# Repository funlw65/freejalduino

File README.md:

[Go back to the main site](https://funlw65.github.io/)
<hr />

## :boom: Welcome!

An alternative to the Arduino board, featuring the PIC18F2550 microcontroller.

Project created using Eagle 7.5.0.

```
 Page done.
```

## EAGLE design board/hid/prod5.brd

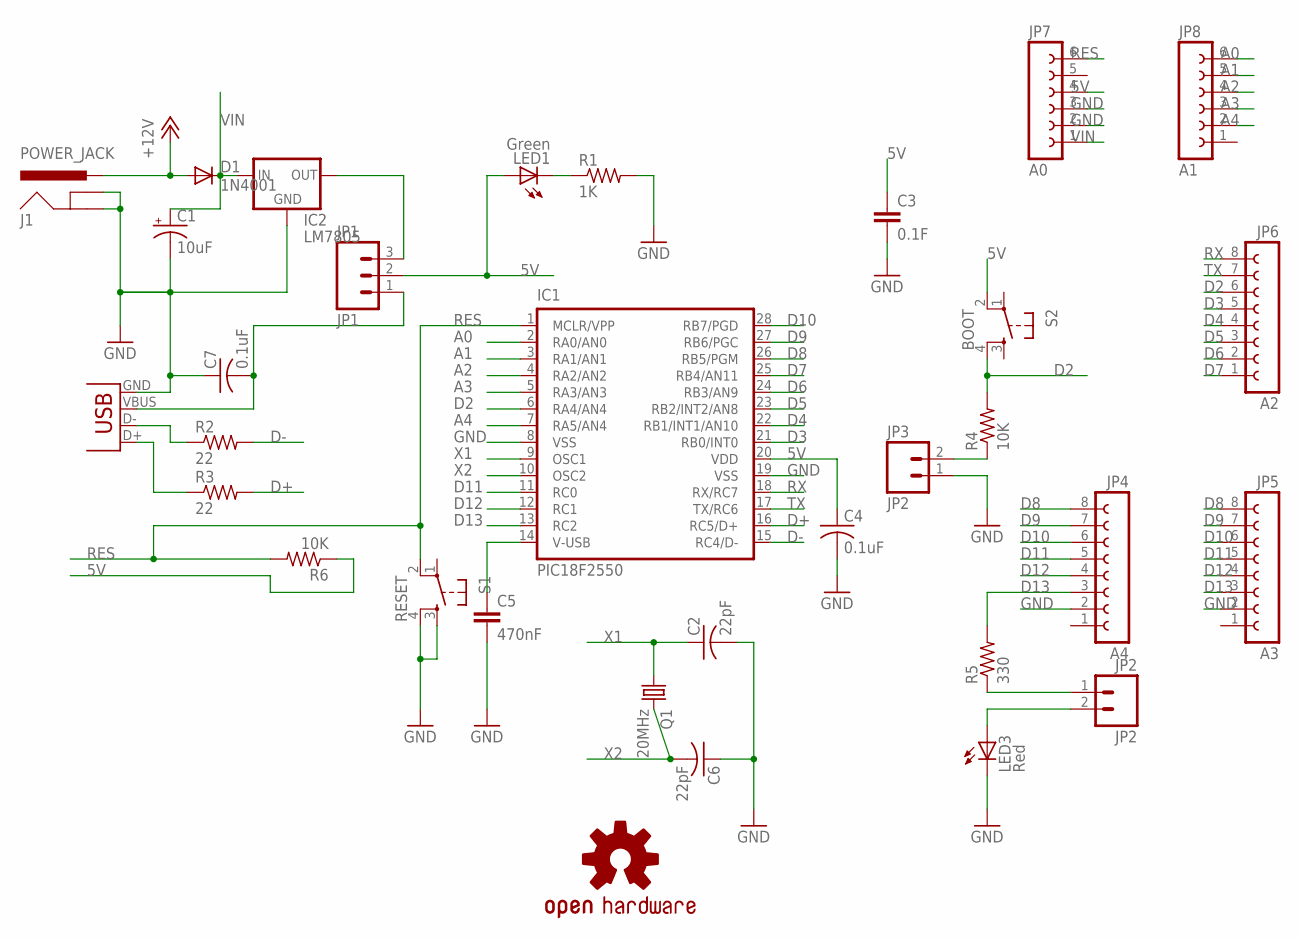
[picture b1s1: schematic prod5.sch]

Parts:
C1: 10uF; CPOL-RADIAL-10UF-25V
C2, C6: 22pF; C025-025X050
C3: 0.1F; CAP-PTH-5MM
C4, C7: 0.1uF; C025-025X050
C5: 470nF; CAP-PTH-5MM
D1: 1N4001; DIODE-1N4001
IC1: PIC18F2550; DIL28-3
IC2: LM7805; 78XXL
J1: POWER_JACK; POWER_JACK_PTH
JP1: JP1; 1X03
JP2, JP3: JP2; 1X02
JP4: A4; FE08
JP5: A3; FE08
JP6: A2; FE08
JP7: A0; FE06
JP8: A1; FE06
LED1: Green; LED3MM
LED3: Red; LED3MM
LOGO1: OSHW-LOGOM; OSHW-LOGO-M
Q1: 20MHz; HC49/S
R1: 1K; 0204/7
R2, R3: 22; 0207/15
R4: 10K; 0207/15
R5: 330; 0204/7
R6: 10K; 0204/7
S1: RESET; TACTILE-PTH
S2: BOOT; TACTILE-PTH
X1: USBPTH; USB-B-PTH

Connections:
5V: C3.1, C4.1, IC1.20 (VDD), JP1.2, JP7.4, LED1.A, R6.1, S2.2
+12V: D1.A, J1.PWR
A0: IC1.2 (RA0/AN0), JP8.6
A1: IC1.3 (RA1/AN1), JP8.5
A2: IC1.4 (RA2/AN2), JP8.4
A3: IC1.5 (RA3/AN3), JP8.3
A4: IC1.7 (RA5/AN4), JP8.2
D2: IC1.6 (RA4/AN4), JP6.6, R4.2, S2.4
D3: IC1.21 (RB0/INT0), JP6.5
D4: IC1.22 (RB1/INT1/AN10), JP6.4
D5: IC1.23 (RB2/INT2/AN8), JP6.3
D6: IC1.24 (RB3/AN9), JP6.2
D7: IC1.25 (RB4/AN11), JP6.1
D8: IC1.26 (RB5/PGM), JP4.8, JP5.8
D9: IC1.27 (RB6/PGC), JP4.7, JP5.7
D10: IC1.28 (RB7/PGD), JP4.6, JP5.6
D11: IC1.11 (RC0), JP4.5, JP5.5
D12: IC1.12 (RC1), JP4.4, JP5.4
D13: IC1.13 (RC2), JP4.3, JP5.3, R5.2
D+: IC1.16 (RC5/D+), R3.2
D-: IC1.15 (RC4/D-), R2.2
GND: C1.2 (-), C2.2, C3.2, C4.2, C5.2, C6.1, C7.1, IC1.8 (VSS), IC1.19 (VSS), IC2.GND, J1.GND, J1.GNDBREAK, JP3.1, JP4.2, JP5.2, JP7.2, JP7.3, LED3.K (C), R1.2, S1.3, S1.4, X1.GND
unnamed: JP3.2, R4.1
unnamed: LED1.K (C), R1.1
unnamed: C7.2, JP1.1, X1.VBUS
unnamed: R2.1, X1.D-
unnamed: R3.1, X1.D+
unnamed: JP2.1, R5.1
unnamed: JP2.2, LED3.A
unnamed: IC2.OUT, JP1.3
unnamed: C5.1, IC1.14 (V-USB)
RES: IC1.1 (MCLR/VPP), JP7.6, R6.2, S1.2
RX: IC1.18 (RX/RC7), JP6.8
TX: IC1.17 (TX/RC6), JP6.7
VIN: C1.1 (+), D1.C, IC2.IN, JP7.1
X1: C2.1, IC1.9 (OSC1), Q1.1
X2: C6.2, IC1.10 (OSC2), Q1.2

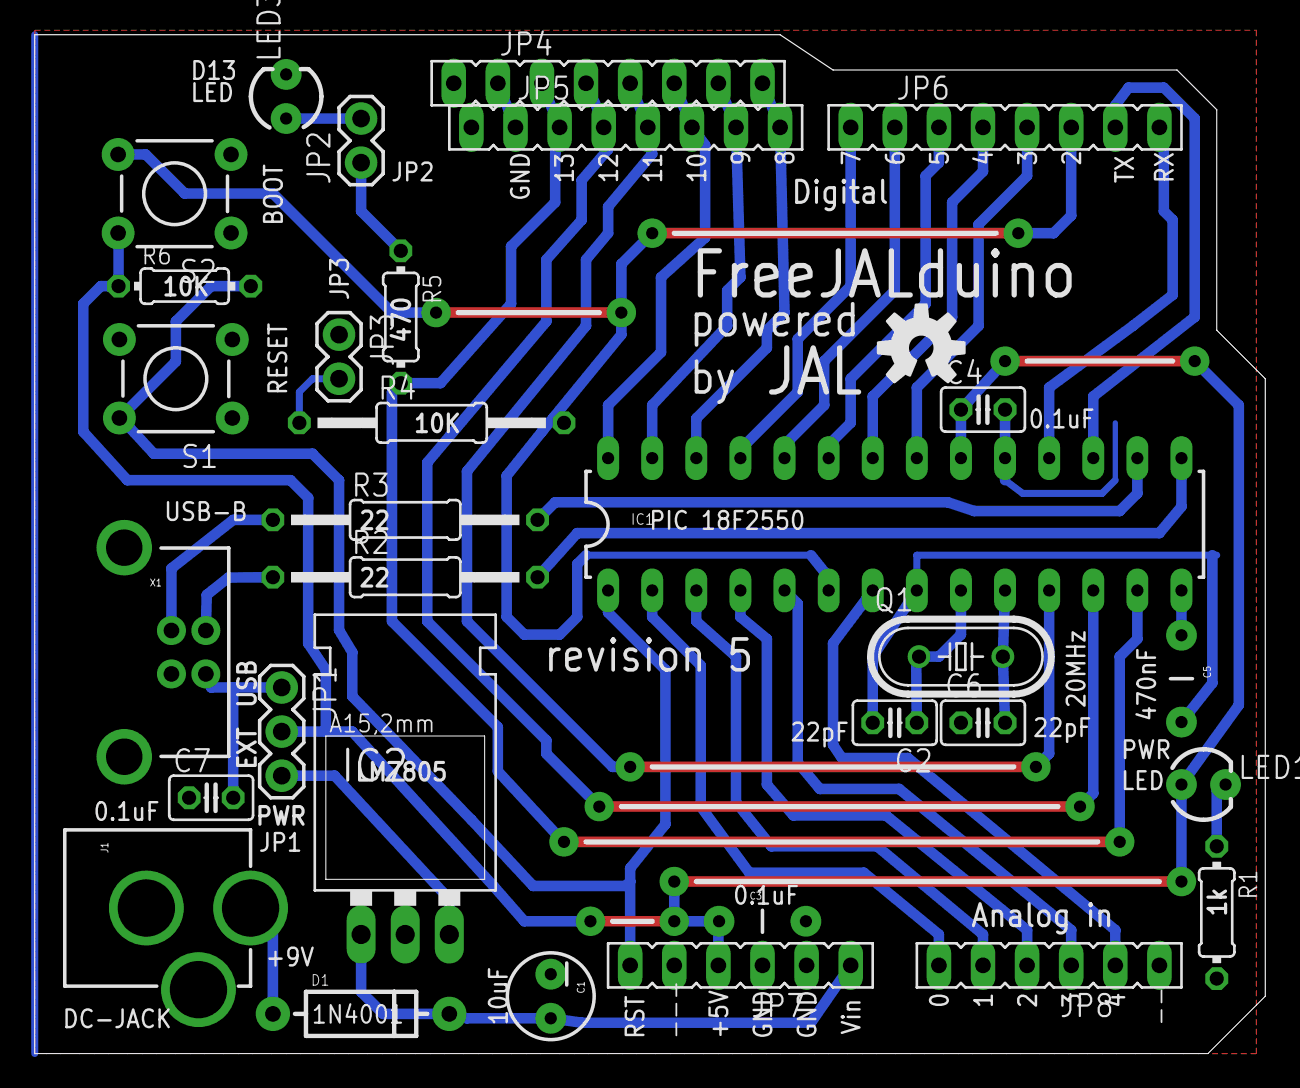
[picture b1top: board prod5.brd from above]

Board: 2 copper layers, 70.9 x 58.7 mm, 32 parts (0 on the bottom side), 37 nets.

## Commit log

2009-10-02 Initial directory structure.
2009-10-04 Created wiki page through web user interface.
2009-10-04 Edited wiki page through web user interface.
2009-10-05 Prepared arduino and shield footprints for gEDA PCB
2009-10-05 Added FreeJALduino board component for Fritzing
2009-10-06 FreeJALduino 2 for gEDA PCB - silk not ready yet. Better design, power LED, testing LED, LM3940 on board. Not tested...
2009-10-06 FreeJALduino gEDA PCB board - (re)placed a missing via.
2009-10-08 Added FreeJALduino MEGA v.3 board and updated FreeJALduino board with a better position for jumper of testing LED.
2010-07-04 Created directory for FreeJALduino html documentation - soon to upload it...
2010-07-11 First release of FreeJALduino5 documentation - written for a friend.
2010-07-11 Eagle files for production at Olimex PCB house - FreeJALduino first board.
2010-08-22 Edited wiki page Documentation_and_Tutorials through web user interface.
2011-08-05 updates for my blogs
2011-08-06 don't update
2011-08-06 repaired
2015-03-17 Migrating wiki contents from Google Code
2017-05-22 Added the serial board in the hid subfolder
2017-05-22 Set theme jekyll-theme-midnight

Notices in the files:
parts and their libraries:
SparkFun-Connectors: Licensing: CC v3.0 Share-Alike You are welcome to use this library for commercial purposes.
